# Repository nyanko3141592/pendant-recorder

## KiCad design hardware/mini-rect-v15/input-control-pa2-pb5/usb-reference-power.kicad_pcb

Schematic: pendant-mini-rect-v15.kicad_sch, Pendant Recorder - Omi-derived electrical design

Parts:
C1, C2, C3, C6, C9, C22, C26: 100n; C_0402_1005Metric
C4: 10u; C_0603_1608Metric
C5: 4.7u; C_0603_1608Metric
C7, C16, C25: 1u; C_0402_1005Metric
C11, C12: 10p tentative; C_0402_1005Metric
C13: 2.2u 10V; C_0402_1005Metric
C14: 2.2u; C_0402_1005Metric
C15: 10u 10V effective >=1u; C_0603_1608Metric
C27: 4.7u effective TBD; C_0603_1608Metric
C28: 10n; C_0402_1005Metric
C29, C32, C33: 100n 10V; C_0402_1005Metric
C30: 50p 50V C0G; C_0402_1005Metric
C31: 1u 10V; C_0402_1005Metric
D6: amber LED 0402 TBD; LED_0402_1005Metric
J1: USB4105-GF-A (candidate); USB_C_GCT_USB4105_GroundLand112
J2: Molex781710003 / DTP401525-XE; Molex_Pico-EZmate_78171-0003_1x03-1MP_P1.20mm_Vertical
J3: TC2030 SWD target pads; Tag-Connect_TC2030-IDC-NL_2x03_P1.27mm_Vertical
J4: DM3D-SF candidate; DM3D_SF_reviewed_candidate
Q3: 2N7002 (VBUS detect); SOT-23
Q4, Q5, Q6, Q7: 2N7002; SOT-23
R1: 0R; R_0402_1005Metric
R2: 10k; R_0402_1005Metric
R3, R4, R12, R13, R15, R22, R36: 100k; R_0402_1005Metric
R6, R7: 5.1k 1%; R_0402_1005Metric
R10: 6.8k 1%; R_0402_1005Metric
R11, R39: 20k 1%; R_0402_1005Metric
R14: 1M; R_0402_1005Metric
R21, R23: 22R tentative; R_0402_1005Metric
R24, R25, R28, R29, R30: 47k; R_0402_1005Metric
R32: 6.8k tentative; R_0402_1005Metric
R33, R34: 1M 1%; R_0402_1005Metric
R35, R43, R47, R48: 10k 1%; R_0402_1005Metric
R37, R38, R40, R45, R46, R49, R50: 100k 1%; R_0402_1005Metric
R41: 7.5k 1%; R_0402_1005Metric
R42: 130k 1%; R_0402_1005Metric
R44: 390k 1%; R_0402_1005Metric
SW1: B3U-1000P (candidate); SW_SPST_B3U-1000P
TH1: NCP18XH103F03RB 10k 1% B3380 candidate; R_0603_1608Metric
TP1, TP2, TP3, TP5, TP6: TestPoint; TestPoint_Pad_D1.0mm
U1: STM32U535CEU6; QFN-48-1EP_7x7mm_P0.5mm_EP5.6x5.6mm
U2: USBLC6-2P6; SOT-666
U3: BQ25185DLHR; Texas_DLH0010A_WSON-10-1EP_2.2x2mm_P0.4mm_EP0.9x1.5mm
U4: TPS7A0233PDBVR; SOT-23-5
U8: IM69D130V01XTSA1; IM69D130_JLC_SMD_trial
U10: TPS22916CYFPR; TPS22916_YFP4
U12: TLV7042DDFR; SOT-23-8
U13: MAX4995CAUT+T; SOT-23-6
U14: SN74HCS74DYYR; Texas_DYY0014A
U15: TLV803EB29DBZR; SOT-23
Y1: 32.768kHz CL=7pF TBD; Crystal_SMD_2012-2Pin_2.0x1.2mm

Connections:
/BAT: C14.1, J2.1 (PACK_PLUS), R33.1, TP1.1, U3.2 (BAT)
/BAT_ADC: C28.1, R33.2, R34.1, U1.11 (PA1)
/BAT_TS: R37.2, TH1.1 (SENSE), U12.2 (INA-), U12.5 (INB+)
/BOOT0: R3.1, U1.44 (PH3)
/BUTTON_N: R4.2, SW1.1, U1.26 (PB13)
/CC1: J1.A5 (CC1), R6.1
/CC2: J1.B5 (CC2), R7.1
/CHARGER_TS: R35.1, U3.6 (TS_MR)
/CHG_ALLOW: R43.1, U1.20 (PB2)
/CHG_GUARD_GATE: Q4.1 (G), R36.1, R43.2, U12.1 (OUTA), U12.7 (OUTB)
/CHG_INHIBIT_GATE: Q4.3 (D), R12.2, U3.4 (CE_N)
/CHG_N: R11.2, U1.27 (PB14), U3.9 (STAT1)
/GND: C1.2, C2.2, C3.2, C4.2, C5.2, C6.2, C7.2, C9.2, C11.2, C12.2, C13.2, C14.2, C15.2, C16.2, C22.2, C25.2, C26.2, C27.2, C28.2, C29.2, C30.2, C31.2, C32.2, C33.2, D6.1 (K), J1.A1 (GND), J1.A12 (GND), J1.B1 (GND), J1.B12 (GND), J1.SH (SHIELD), J2.3 (PACK_MINUS), J3.5 (GND), J4.6 (VSS), J4.SH (SHELL), Q3.2 (S), Q4.2 (S), Q5.2 (S), Q6.2 (S), Q7.2 (S), R3.2, R6.2, R7.2, R10.2, R14.2, R22.2, R34.2, R35.2, R36.2, R39.2, R41.2, R42.2, R44.2, R46.2, R49.2, R50.2, SW1.2, TH1.2 (RETURN), TP6.1, U1.8 (VSSA), U1.23 (VSS), U1.35 (VSS), U1.47 (VSS), U1.49 (VSS), U2.2 (GND), U3.5 (GND), U3.11 (EP), U4.2 (GND), U8.4 (SELECT), U8.5 (GND), U10.B1 (GND), U12.4 (VEE), U13.2 (GND), U14.7 (GND), U14.11 (2CLK), U14.12 (2D), U14.13 (2CLR_N), U15.1 (GND)
/ILIM_VSET: R42.1, U3.7 (ILIM_VSET)
/ISET: C30.1, R10.1, U3.8 (ISET)
/LSE_IN: C11.1, U1.3 (PC14), Y1.1
/LSE_OUT: C12.1, U1.4 (PC15), Y1.2
/NRST: C9.1, J3.3 (nRESET), R2.2, U1.7 (NRST)
/PDM_CLK: R21.2, U8.3 (CLOCK)
/PDM_CLK_MCU: R21.1, U1.39 (PB3)
/PDM_DATA: U1.40 (PB4), U8.1 (DATA)
/SD_CLK: J4.5 (CLK), R23.2
/SD_CLK_MCU: R23.1, U1.15 (PA5)
/SD_CS_N: J4.2 (DAT3_CS), R28.2, U1.14 (PA4)
/SD_DAT1: J4.8 (DAT1), R29.2
/SD_DAT2: J4.1 (DAT2), R30.2
/SD_EN: R22.1, U1.41 (PB5), U10.B2 (ON)
/SD_MISO: J4.7 (DAT0_DO), R25.2, U1.16 (PA6)
/SD_MOSI: J4.3 (CMD_DI), R24.2, U1.17 (PA7)
/SD_V3: C26.1, C27.1, J4.4 (VDD), R24.1, R25.1, R28.1, R29.1, R30.1, TP5.1, U10.A1 (VOUT)
/STATUS_LED: R32.1, U1.29 (PA8)
/STATUS_LED_A: D6.2 (A), R32.2
/SWCLK: J3.4 (SWCLK), U1.37 (PA14)
/SWDIO: J3.2 (SWDIO), U1.34 (PA13)
/SYS: C15.1, TP2.1, U3.1 (SYS), U4.1 (IN), U4.3 (EN)
/TS_COLD_REF: R38.2, R39.1, U12.3 (INA+)
/TS_HOT_REF: R40.2, R41.1, U12.6 (INB-)
/USB_DM: J1.A7 (D-), J1.B7 (D-), U1.32 (PA11), U2.3 (IO2), U2.4 (IO2)
/USB_DP: J1.A6 (D+), J1.B6 (D+), U1.33 (PA12), U2.1 (IO1), U2.6 (IO1)
/USB_HIGH_BUDGET: Q5.1 (G), R46.1, U1.42 (PB6)
/USB_HIGH_BUDGET_DRAIN: Q5.3 (D), R45.2
/USB_ILIM_SET: R44.1, R45.1, U13.3 (SETI)
/USB_INPUT_ON: U13.4 (ON), U14.6 (1Q_N)
/USB_LATCH_CLEAR_N: Q7.3 (D), R48.2, U14.1 (1CLR_N), U15.2 (RESET_N)
/USB_LATCH_CLOCK: Q6.3 (D), R47.2, U14.3 (1CLK)
/USB_RESUME_PULSE: Q7.1 (G), R50.1, U1.19 (PB1)
/USB_SUSPEND_PULSE: Q6.1 (G), R49.1, U1.12 (PA2)
/V3V3: C1.1, C2.1, C3.1, C4.1, C16.1, C22.1, C25.1, J3.1 (VTref), R1.1, R2.1, R4.1, R11.1, R15.1, TP3.1, U1.1 (VBAT), U1.24 (VDD), U1.36 (VDD), U1.48 (VDD), U4.5 (OUT), U8.2 (VDD), U10.A2 (VIN)
/VBUS: C31.1, C32.1, C33.1, J1.A4 (VBUS), J1.A9 (VBUS), J1.B4 (VBUS), J1.B9 (VBUS), R13.1, R47.1, R48.1, U2.5 (VBUS), U13.5 (IN), U14.2 (1D), U14.4 (1PRE_N), U14.10 (2PRE_N), U14.14 (VCC), U15.3 (VDD)
/VBUS_GATE: Q3.1 (G), R13.2, R14.1
/VBUS_LIMITED: C13.1, C29.1, R12.1, R37.1, R38.1, R40.1, U3.10 (IN), U12.8 (VCC), U13.1 (OUT)
/VBUS_N: Q3.3 (D), R15.2, U1.10 (PA0)
/VCAP: C5.1, U1.22 (VCAP)
/VDDA: C6.1, C7.1, R1.2, U1.9 (VDDA)

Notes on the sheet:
01 MCU / RTC / UI
02 USB-C / CHARGER
03 POWER / FUEL GAUGE
04 AUDIO / SD / INDICATORS
ENGINEERING DRAFT - NOT FOR FABRICATION - See hardware/mini-rect-v15/README.md

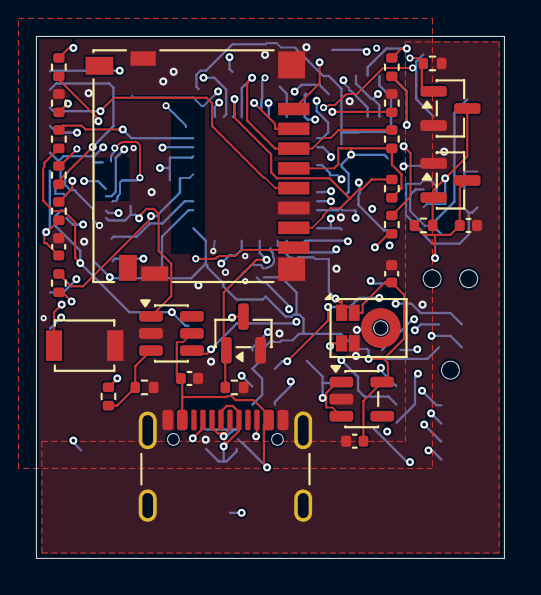
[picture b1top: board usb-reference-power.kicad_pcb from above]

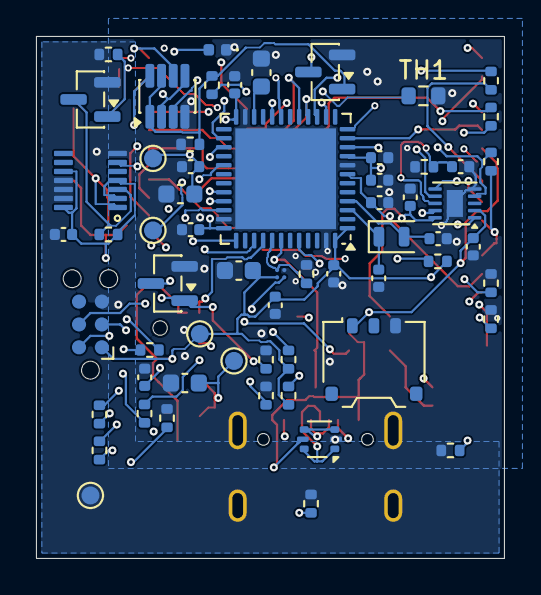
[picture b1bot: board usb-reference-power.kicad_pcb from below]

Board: 6 copper layers, 26.0 x 29.0 mm, 91 parts (61 on the bottom side), 54 nets.

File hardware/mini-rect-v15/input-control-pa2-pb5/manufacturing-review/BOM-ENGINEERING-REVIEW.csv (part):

Reference,Design value,Footprint,Supplier part number,Qualification status
U1,STM32U535CEU6,Package_DFN_QFN:QFN-48-1EP_7x7mm_P0.5mm_EP5.6x5.6mm,,Exact orderable SKU and matching still required
C1,100n,Capacitor_SMD:C_0402_1005Metric,,Exact orderable SKU and matching still required
C4,10u,Capacitor_SMD:C_0603_1608Metric,,Exact orderable SKU and matching still required
C9,100n,Capacitor_SMD:C_0402_1005Metric,,Exact orderable SKU and matching still required
R2,10k,Resistor_SMD:R_0402_1005Metric,,Exact orderable SKU and matching still required
Y1,32.768kHz CL=7pF TBD,Crystal:Crystal_SMD_2012-2Pin_2.0x1.2mm,,Exact orderable SKU and matching still required
C11,10p tentative,Capacitor_SMD:C_0402_1005Metric,,Exact orderable SKU and matching still required
C12,10p tentative,Capacitor_SMD:C_0402_1005Metric,,Exact orderable SKU and matching still required
SW1,B3U-1000P (candidate),Button_Switch_SMD:SW_SPST_B3U-1000P,,Exact orderable SKU and matching still required
R4,100k,Resistor_SMD:R_0402_1005Metric,,Exact orderable SKU and matching still required
J1,USB4105-GF-A (candidate),PendantD1:USB_C_GCT_USB4105_GroundLand112,,Exact orderable SKU and matching still required
R6,5.1k 1%,Resistor_SMD:R_0402_1005Metric,,Exact orderable SKU and matching still required
R7,5.1k 1%,Resistor_SMD:R_0402_1005Metric,,Exact orderable SKU and matching still required
U2,USBLC6-2P6,Package_TO_SOT_SMD:SOT-666,,Exact orderable SKU and matching still required
C13,2.2u 10V,Capacitor_SMD:C_0402_1005Metric,,Exact orderable SKU and matching still required
U3,BQ25185DLHR,Package_DFN_QFN:Texas_DLH0010A_WSON-10-1EP_2.2x2mm_P0.4mm_EP0.9x1.5mm,,Exact orderable SKU and matching still required
R10,6.8k 1%,Resistor_SMD:R_0402_1005Metric,,Exact orderable SKU and matching still required
R11,20k 1%,Resistor_SMD:R_0402_1005Metric,,Exact orderable SKU and matching still required
C14,2.2u,Capacitor_SMD:C_0402_1005Metric,,Exact orderable SKU and matching still required
J2,Molex781710003 / DTP401525-XE,Connector_Molex:Molex_Pico-EZmate_78171-0003_1x03-1MP_P1.20mm_Vertical,,Exact orderable SKU and matching still required
R12,100k,Resistor_SMD:R_0402_1005Metric,,Exact orderable SKU and matching still required
C15,10u 10V effective >=1u,Capacitor_SMD:C_0603_1608Metric,,Exact orderable SKU and matching still required
U4,TPS7A0233PDBVR,Package_TO_SOT_SMD:SOT-23-5,,Exact orderable SKU and matching still required
C16,1u,Capacitor_SMD:C_0402_1005Metric,,Exact orderable SKU and matching still required
U8,IM69D130V01XTSA1,Pendant:IM69D130_JLC_SMD_trial,,Exact orderable SKU and matching still required
R21,22R tentative,Resistor_SMD:R_0402_1005Metric,,Exact orderable SKU and matching still required
C22,100n,Capacitor_SMD:C_0402_1005Metric,,Exact orderable SKU and matching still required
U10,TPS22916CYFPR,Pendant:TPS22916_YFP4,,Exact orderable SKU and matching still required
R22,100k,Resistor_SMD:R_0402_1005Metric,,Exact orderable SKU and matching still required
C25,1u,Capacitor_SMD:C_0402_1005Metric,,Exact orderable SKU and matching still required
R23,22R tentative,Resistor_SMD:R_0402_1005Metric,,Exact orderable SKU and matching still required
R24,47k,Resistor_SMD:R_0402_1005Metric,,Exact orderable SKU and matching still required
R25,47k,Resistor_SMD:R_0402_1005Metric,,Exact orderable SKU and matching still required
R28,47k,Resistor_SMD:R_0402_1005Metric,,Exact orderable SKU and matching still required
C26,100n,Capacitor_SMD:C_0402_1005Metric,,Exact orderable SKU and matching still required
C27,4.7u effective TBD,Capacitor_SMD:C_0603_1608Metric,,Exact orderable SKU and matching still required
R32,6.8k tentative,Resistor_SMD:R_0402_1005Metric,,Exact orderable SKU and matching still required
D6,amber LED 0402 TBD,LED_SMD:LED_0402_1005Metric,,Exact orderable SKU and matching still required
C2,100n,Capacitor_SMD:C_0402_1005Metric,,Exact orderable SKU and matching still required
C3,100n,Capacitor_SMD:C_0402_1005Metric,,Exact orderable SKU and matching still required
C5,4.7u,Capacitor_SMD:C_0603_1608Metric,,Exact orderable SKU and matching still required
C6,100n,Capacitor_SMD:C_0402_1005Metric,,Exact orderable SKU and matching still required
C7,1u,Capacitor_SMD:C_0402_1005Metric,,Exact orderable SKU and matching still required
R1,0R,Resistor_SMD:R_0402_1005Metric,,Exact orderable SKU and matching still required
R3,100k,Resistor_SMD:R_0402_1005Metric,,Exact orderable SKU and matching still required
Q3,2N7002 (VBUS detect),Package_TO_SOT_SMD:SOT-23,,Exact orderable SKU and matching still required
R13,100k,Resistor_SMD:R_0402_1005Metric,,Exact orderable SKU and matching still required
R14,1M,Resistor_SMD:R_0402_1005Metric,,Exact orderable SKU and matching still required
R15,100k,Resistor_SMD:R_0402_1005Metric,,Exact orderable SKU and matching still required
R33,1M 1%,Resistor_SMD:R_0402_1005Metric,,Exact orderable SKU and matching still required
R34,1M 1%,Resistor_SMD:R_0402_1005Metric,,Exact orderable SKU and matching still required
C28,10n,Capacitor_SMD:C_0402_1005Metric,,Exact orderable SKU and matching still required
R35,10k 1%,Resistor_SMD:R_0402_1005Metric,,Exact orderable SKU and matching still required
R36,100k,Resistor_SMD:R_0402_1005Metric,,Exact orderable SKU and matching still required
R37,100k 1%,Resistor_SMD:R_0402_1005Metric,,Exact orderable SKU and matching still required
R38,100k 1%,Resistor_SMD:R_0402_1005Metric,,Exact orderable SKU and matching still required
R39,20k 1%,Resistor_SMD:R_0402_1005Metric,,Exact orderable SKU and matching still required
R40,100k 1%,Resistor_SMD:R_0402_1005Metric,,Exact orderable SKU and matching still required
R41,7.5k 1%,Resistor_SMD:R_0402_1005Metric,,Exact orderable SKU and matching still required
U12,TLV7042DDFR,Package_TO_SOT_SMD:SOT-23-8,,Exact orderable SKU and matching still required
Q4,2N7002,Package_TO_SOT_SMD:SOT-23,,Exact orderable SKU and matching still required
C29,100n 10V,Capacitor_SMD:C_0402_1005Metric,,Exact orderable SKU and matching still required
R42,130k 1%,Resistor_SMD:R_0402_1005Metric,,Exact orderable SKU and matching still required
C30,50p 50V C0G,Capacitor_SMD:C_0402_1005Metric,,Exact orderable SKU and matching still required
R43,10k 1%,Resistor_SMD:R_0402_1005Metric,,Exact orderable SKU and matching still required
J4,DM3D-SF candidate,Pendant:DM3D_SF_reviewed_candidate,,Exact orderable SKU and matching still required
R29,47k,Resistor_SMD:R_0402_1005Metric,,Exact orderable SKU and matching still required
R30,47k,Resistor_SMD:R_0402_1005Metric,,Exact orderable SKU and matching still required
TH1,NCP18XH103F03RB 10k 1% B3380 candidate,Resistor_SMD:R_0603_1608Metric,,Exact orderable SKU and matching still required
U13,MAX4995CAUT+T,Package_TO_SOT_SMD:SOT-23-6,,Exact orderable SKU and matching still required
U14,SN74HCS74DYYR,Pendant_Input:Texas_DYY0014A,,Exact orderable SKU and matching still required
U15,TLV803EB29DBZR,Package_TO_SOT_SMD:SOT-23,,Exact orderable SKU and matching still required
R44,390k 1%,Resistor_SMD:R_0402_1005Metric,,Exact orderable SKU and matching still required
R45,100k 1%,Resistor_SMD:R_0402_1005Metric,,Exact orderable SKU and matching still required
Q5,2N7002,Package_TO_SOT_SMD:SOT-23,,Exact orderable SKU and matching still required
R46,100k 1%,Resistor_SMD:R_0402_1005Metric,,Exact orderable SKU and matching still required
R47,10k 1%,Resistor_SMD:R_0402_1005Metric,,Exact orderable SKU and matching still required
R48,10k 1%,Resistor_SMD:R_0402_1005Metric,,Exact orderable SKU and matching still required
Q6,2N7002,Package_TO_SOT_SMD:SOT-23,,Exact orderable SKU and matching still required
Q7,2N7002,Package_TO_SOT_SMD:SOT-23,,Exact orderable SKU and matching still required
R49,100k 1%,Resistor_SMD:R_0402_1005Metric,,Exact orderable SKU and matching still required
R50,100k 1%,Resistor_SMD:R_0402_1005Metric,,Exact orderable SKU and matching still required
C31,1u 10V,Capacitor_SMD:C_0402_1005Metric,,Exact orderable SKU and matching still required
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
